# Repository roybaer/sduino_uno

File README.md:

# sduino UNO

The __sduino UNO__ is an attempt at creating a mechanically and electrically Arduino-UNO-compatible development board based on the __STM8S105K6__ microcontroller.
Both, mechanical and electrical design are to a notable degree based on the [Arduino UNO board](https://store.arduino.cc/arduino-uno-rev3).

Components and silkscreen can be viewed in more detail in a [picture of the component side](img/front.jpg) and a [picture of the back side](img/back.jpg) of the assembled board.

## Pin mapping

Number | UNO pin name | ATMEGA328 pin name | STM8S105K6 pin name
-------|--------------|--------------------|----------------------------------------
0      | IO0/RX       | PD0/RXD            | PD6/UART2_RX
1      | IO1/TX       | PD1/TXD            | PD5/UART2_TX
2      | IO2          | PD2/INT0           | PD7/TLI [TIM1_CH4]
3      | IO3          | PD3/INT1/OC2B      | PD2 (HS)/TIM3_CH1 [TIM2_CH3]
4      | IO4          | PD4/T0/XCK         | PD0 (HS)/TIM3_CH2 [TIM1_BKIN]/[CLK_COO]
5      | IO5          | PD5/T1/OC0B        | PD4 (HS)/TIM2_CH1 [BEEP]
6      | IO6          | PD6/AIN0/OC0A      | PD3 (HS)/TIM2_CH2/ADC_ETR
7      | IO7          | PD7/AIN1           | PD1 (HS)/SWIM
8      | IO8          | PB0/ICP1/CLKO      | PC1 (HS)/TIM1_CH1/UART2_CK
9      | IO9          | PB1/OC1A           | PC3 (HS)/TIM1_CH3
10     | IO10/~~SS~~  | PB2/NSS/OC1B       | PC4 (HS)/TIM1_CH4
11     | IO11/MOSI    | PB3/MOSI/OC2A      | PC6 (HS)/SPI_MOSI
12     | IO12/MISO    | PB4/MISO           | PC7 (HS)/SPI_MISO
13     | IO13/SCK     | PB5/SCK            | PC5 (HS)/SPI_SCK
14     | AD0          | PC0/ADC0           | PB0/AIN0 [TIM1_CH1N]
15     | AD1          | PC1/ADC1           | PB1/AIN1 [TIM1_CH2N]
16     | AD2          | PC2/ADC2           | PB2/AIN2 [TIM1_CH3N]
17     | AD3          | PC3/ADC3           | PB3/AIN3 [TIM1_ETR]
18     | AD4/SDA      | PC4/ADC4           | PB5/AIN5 [I2C_SDA]
19     | AD5/SCL      | PC5/ADC5           | PB4/AIN4 [I2C_SCL]
20     | AD6          | --                 | --
21     | AD7          | --                 | --
_22_   | AREF         | AREF               | PF4/AIN12
_23_   | _IO23_       | --                 | PC2 (HS)/TIM1_CH2
_24_   | _IO24/SS_    | --                 | PE5/SPI_NSS
--     | RESET        | NRESET             | NRST
--     | --           | PB6/TOSC1/XTAL1    | PA1/OSCIN
--     | --           | PB7/TOSC2/XTAL2    | PA2/OSCOUT

For evaluation purposes, most of the sduino UNO's functionality can be imitated with an STM8-DISCOVERY board and a USB to Serial converter, as described in [this document](docs/discovery.md).

## Differences

The following paragraphs highlight the most important differences between Arduino UNO and sduino UNO.

### Mechanical

The gap between the upper socket strips has been reduced from 0.06 to 0.05 inches.
This should not significantly impact mechanical compatibility with Arduino UNO shields and increases the available radius around the center of the upper left M3 mounting hole from 2.286 to 2.54 millimeters, which should be just enough to fit in a standard M3 spacer (5mm wrench).

### Electrical

Most importantly, the sduino UNO can be switched between 5V and 3.3V operating voltage.
The RX and TX LEDs are connected to the RX and TX lines (IO pin 0 and 1, respectively) via 1k resistors, rather than to the USB interface chip.

### Functional

Like many Arduino UNO clones, the sduino UNO uses a CH340G USB to serial converter instead of an Atmega16U2 for communication with the host PC.
The USB interface Chip therefore cannot be repurposed as a coprocessor or keyboard/mouse simulator.

There is no analog comparator in the STM8S105K6 microcontroller and AREF is actually an additional analog input.
Its use as reference voltage for A/D conversion has to be imitated in software.
IO11 has no hardware PWM functionality for analog_write, IO8 and IO4 have.
IO2, AD0, AD1 and AD2 can be used as PWM outputs via alternate function mapping.

Likewise, IO10 does not serve as hardware-slave-select line for the SPI bus.
This, however, can mostly be overcome by software-emulation, because the STM8 allows for slave-select to be controlled in software, e.g. in an interrupt handler.
The actual slave-select line has been made available via an exra pin.

### Software

Unfortunately, there is no free C++ compiler available for the STM8 platform, yet.
The Arduino language along with the large pool of existing Arduino sketches can therefore not be used without modifications.

Fortunately, there is the C-based [sduino library](https://github.com/tenbaht/sduino) that in fact inspired the creation of the sduino UNO and that this board borrows its name from.
By using the sduino library, the changes required to run many exsting Arduino sketches on an STM8 platform can be kept within manageable bounds.

Possibilities to bring C++ support to the STM8 platform with a free compiler are being evaluated.

## Copying

Even though the sduino UNO CAD files have been created from scratch and the design is not identical, to avoid legal ambiguity, the CAD files for the sduino UNO board are released under the same creative commons license as those of the Arduino UNO board:

This work is licensed under the Creative Commons Attribution-ShareAlike 2.5 Generic License. To view a copy of this license, visit http://creativecommons.org/licenses/by-sa/2.5/ or send a letter to Creative Commons, PO Box 1866, Mountain View, CA 94042, USA.

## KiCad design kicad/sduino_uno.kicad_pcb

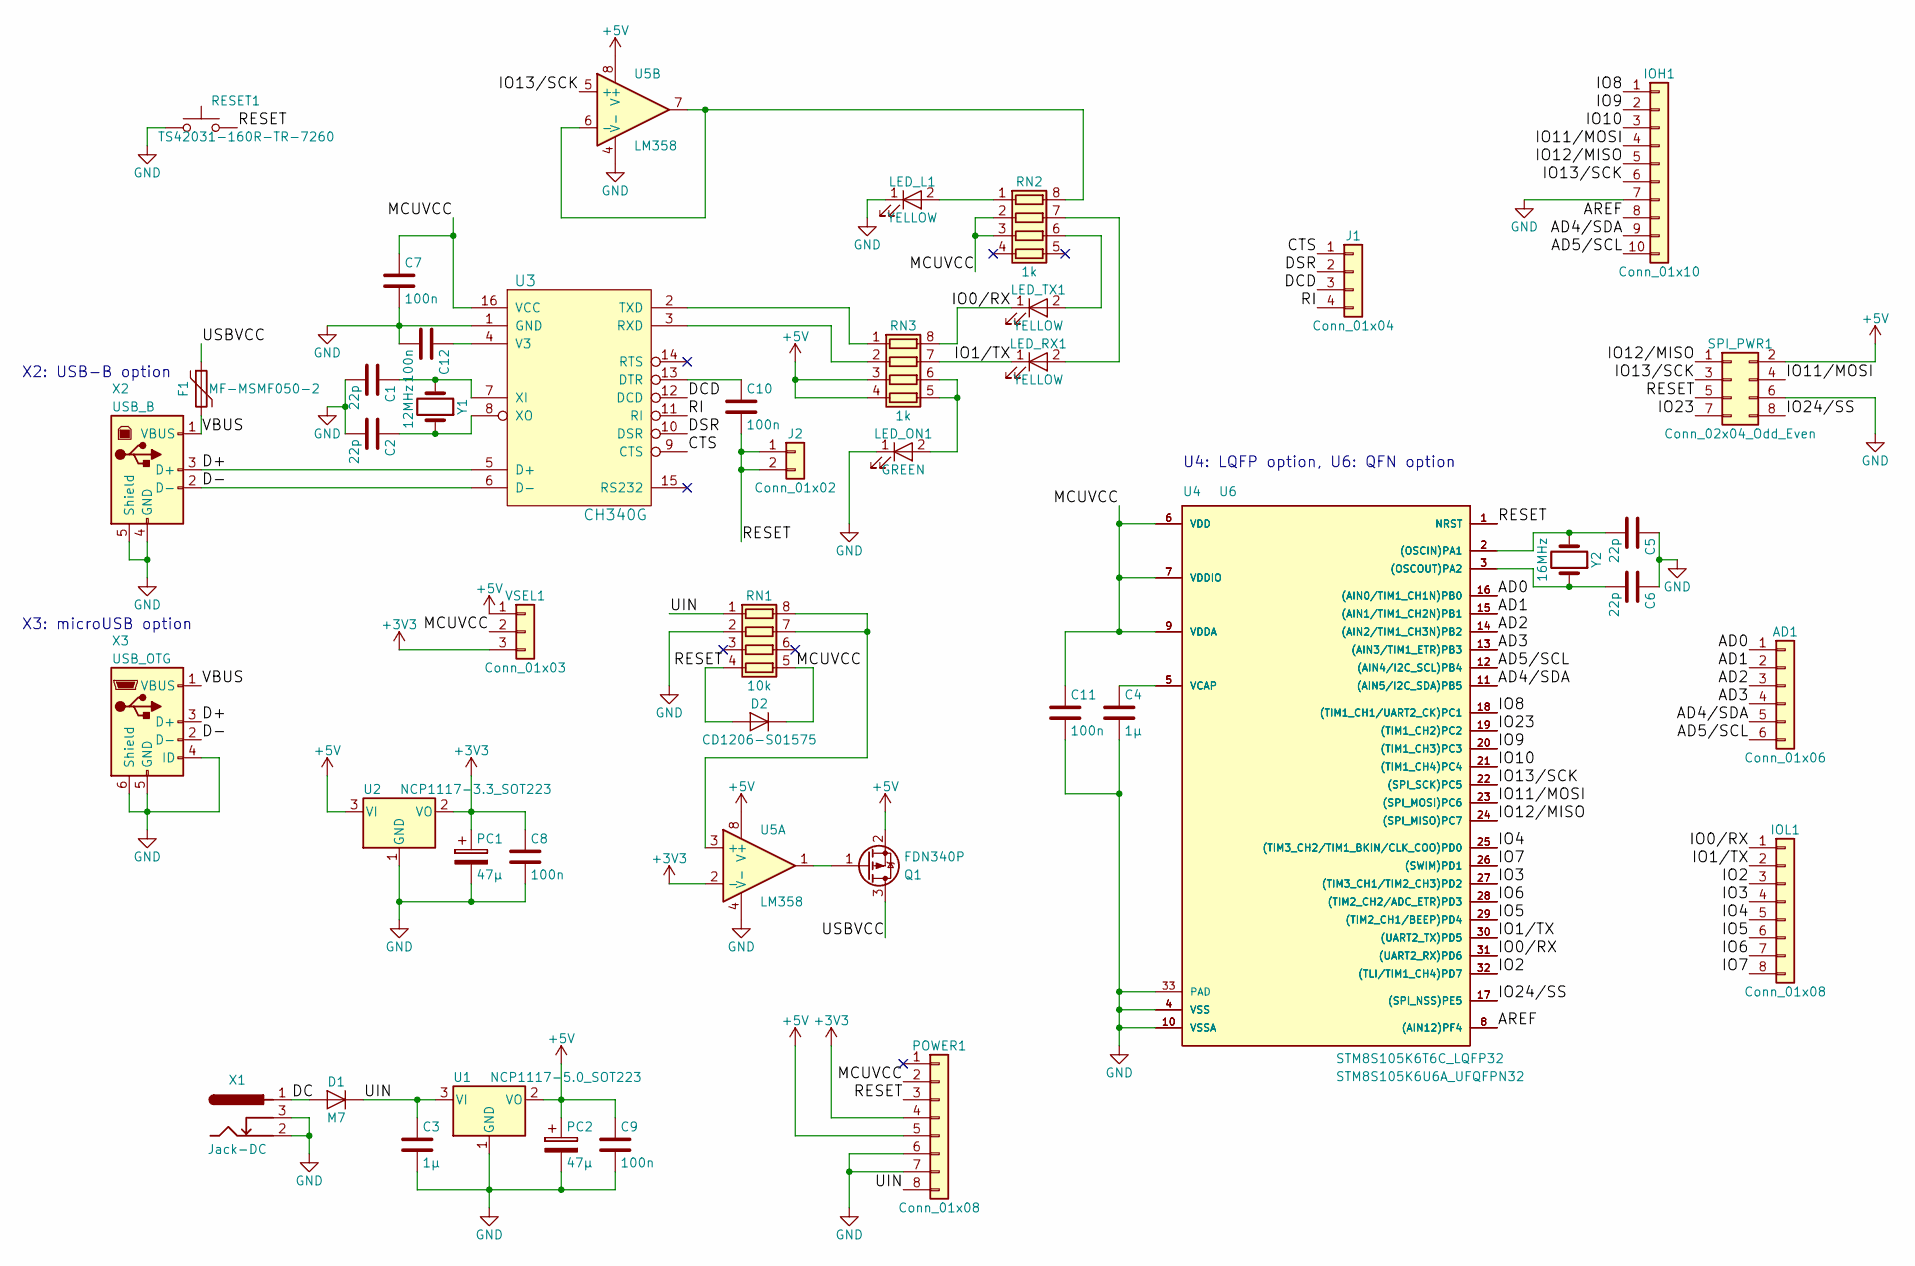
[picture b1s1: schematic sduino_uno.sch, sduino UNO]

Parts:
AD1: Conn_01x06; Socket_Strip_Straight_1x06_Pitch2.54mm
C1, C2, C5, C6: 22p; C_0603
C3, C4: 1µ; C_0805
C7, C8, C9, C10, C11, C12: 100n; C_0603
D1: M7; D_SMA
D2: CD1206-S01575; D_1206
F1: MF-MSMF050-2; R_1812
IOH1: Conn_01x10; Socket_Strip_Straight_1x10_Pitch2.54mm
IOL1: Conn_01x08; Socket_Strip_Straight_1x08_Pitch2.54mm
J1: Conn_01x04; Pin_Header_Straight_1x04_Pitch2.54mm
J2: Conn_01x02; Pin_Header_Straight_1x02_Pitch2.54mm
LED_L1: YELLOW; LED_0805
LED_ON1: GREEN; LED_0805
LED_RX1: YELLOW; LED_0805
LED_TX1: YELLOW; LED_0805
PC1, PC2: 47µ; CP_Elec_6.3x5.8
POWER1: Conn_01x08; Socket_Strip_Straight_1x08_Pitch2.54mm
Q1: FDN340P; SOT-23
RESET1: TS42031-160R-TR-7260; SW_SPST_B3S-1000
RN1: 10k; R_Array_Concave_4x0603
RN2, RN3: 1k; R_Array_Concave_4x0603
SPI_PWR1: Conn_02x04_Odd_Even; Pin_Header_Straight_2x04_Pitch2.54mm
U1: NCP1117-5.0_SOT223; SOT-223-3Lead_TabPin2
U2: NCP1117-3.3_SOT223; SOT-223-3Lead_TabPin2
U3: CH340G; SOIC-16_3.9x9.9mm_Pitch1.27mm
U4: STM8S105K6T6C_LQFP32; LQFP-32_7x7mm_Pitch0.8mm
U5: LM358; SOIC-8_3.9x4.9mm_Pitch1.27mm
U6: STM8S105K6U6A_UFQFPN32; QFN-32-1EP_5x5mm_Pitch0.5mm
VSEL1: Conn_01x03; Pin_Header_Straight_1x03_Pitch2.54mm
X1: Jack-DC; JACK_ALIM
X2: USB_B
X3: USB_OTG; USB_Micro-B_Molex_47346-0001
Y1: 12MHz; Crystal_HC49-4H_Vertical
Y2: 16MHz; Crystal_HC49-4H_Vertical

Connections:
+3V3: C8.1, PC1.1, POWER1.4, U2.2 (VO), U5.2 (-), VSEL1.3
+5V: C9.1, PC2.1, POWER1.5, Q1.2 (S), RN3.3 (R3.1), RN3.4 (R4.1), SPI_PWR1.2, U1.2 (VO), U2.3 (VI), U5.8 (V+), VSEL1.1
/AD0: AD1.1, U4.16 ((AIN0/TIM1_CH1N)PB0), U6.16 ((AIN0/TIM1_CH1N)PB0)
/AD1: AD1.2, U4.15 ((AIN1/TIM1_CH2N)PB1), U6.15 ((AIN1/TIM1_CH2N)PB1)
/AD2: AD1.3, U4.14 ((AIN2/TIM1_CH3N)PB2), U6.14 ((AIN2/TIM1_CH3N)PB2)
/AD3: AD1.4, U4.13 ((AIN3/TIM1_ETR)PB3), U6.13 ((AIN3/TIM1_ETR)PB3)
/AD4/SDA: AD1.5, IOH1.9, U4.11 ((AIN5/I2C_SDA)PB5), U6.11 ((AIN5/I2C_SDA)PB5)
/AD5/SCL: AD1.6, IOH1.10, U4.12 ((AIN4/I2C_SCL)PB4), U6.12 ((AIN4/I2C_SCL)PB4)
/AREF: IOH1.8, U4.8 ((AIN12)PF4), U6.8 ((AIN12)PF4)
/CTS: J1.1, U3.9 (CTS)
/D+: U3.5 (D+), X2.3 (D+), X3.3 (D+)
/D-: U3.6 (D-), X2.2 (D-), X3.2 (D-)
/DC: D1.2 (A), X1.1
/DCD: J1.3, U3.12 (DCD)
/DSR: J1.2, U3.10 (DSR)
/IO0/RX: IOL1.1, LED_TX1.1 (K), RN3.8 (R1.2), U4.31 ((UART2_RX)PD6), U6.31 ((UART2_RX)PD6)
/IO1/TX: IOL1.2, LED_RX1.1 (K), RN3.7 (R2.2), U4.30 ((UART2_TX)PD5), U6.30 ((UART2_TX)PD5)
/IO2: IOL1.3, U4.32 ((TLI/TIM1_CH4)PD7), U6.32 ((TLI/TIM1_CH4)PD7)
/IO3: IOL1.4, U4.27 ((TIM3_CH1/TIM2_CH3)PD2), U6.27 ((TIM3_CH1/TIM2_CH3)PD2)
/IO4: IOL1.5, U4.25 ((TIM3_CH2/TIM1_BKIN/CLK_COO)PD0), U6.25 ((TIM3_CH2/TIM1_BKIN/CLK_COO)PD0)
/IO5: IOL1.6, U4.29 ((TIM2_CH1/BEEP)PD4), U6.29 ((TIM2_CH1/BEEP)PD4)
/IO6: IOL1.7, U4.28 ((TIM2_CH2/ADC_ETR)PD3), U6.28 ((TIM2_CH2/ADC_ETR)PD3)
/IO7: IOL1.8, U4.26 ((SWIM)PD1), U6.26 ((SWIM)PD1)
/IO8: IOH1.1, U4.18 ((TIM1_CH1/UART2_CK)PC1), U6.18 ((TIM1_CH1/UART2_CK)PC1)
/IO9: IOH1.2, U4.20 ((TIM1_CH3)PC3), U6.20 ((TIM1_CH3)PC3)
/IO10: IOH1.3, U4.21 ((TIM1_CH4)PC4), U6.21 ((TIM1_CH4)PC4)
/IO11/MOSI: IOH1.4, SPI_PWR1.4, U4.23 ((SPI_MOSI)PC6), U6.23 ((SPI_MOSI)PC6)
/IO12/MISO: IOH1.5, SPI_PWR1.1, U4.24 ((SPI_MISO)PC7), U6.24 ((SPI_MISO)PC7)
/IO13/SCK: IOH1.6, SPI_PWR1.3, U4.22 ((SPI_SCK)PC5), U5.5 (+), U6.22 ((SPI_SCK)PC5)
/IO23: SPI_PWR1.7, U4.19 ((TIM1_CH2)PC2), U6.19 ((TIM1_CH2)PC2)
/IO24/SS: SPI_PWR1.8, U4.17 ((SPI_NSS)PE5), U6.17 ((SPI_NSS)PE5)
/MCUVCC: C7.1, C11.1, D2.1 (K), POWER1.2, RN1.5 (R4.2), RN2.2 (R2.1), RN2.3 (R3.1), U3.16 (VCC), U4.6 (VDD), U4.7 (VDDIO), U4.9 (VDDA), U6.6 (VDD), U6.7 (VDDIO), U6.9 (VDDA), VSEL1.2
/RESET: C10.2, D2.2 (A), J2.1, J2.2, POWER1.3, RESET1.2, RN1.4 (R4.1), SPI_PWR1.5, U4.1 (NRST), U6.1 (NRST)
/RI: J1.4, U3.11 (RI)
/UIN: C3.1, D1.1 (K), POWER1.8, RN1.1 (R1.1), U1.3 (VI)
/USBVCC: F1.1, Q1.3 (D)
/VBUS: F1.2, X2.1 (VBUS), X3.1 (VBUS)
GND: C1.2, C2.2, C3.2, C4.2, C5.1, C6.1, C7.2, C8.2, C9.2, C11.2, C12.2, IOH1.7, LED_L1.1 (K), LED_ON1.1 (K), PC1.2, PC2.2, POWER1.6, POWER1.7, RESET1.1, RN1.2 (R2.1), SPI_PWR1.6, U1.1 (GND), U2.1 (GND), U3.1 (GND), U4.4 (VSS), U4.10 (VSSA), U5.4 (V-), U6.4 (VSS), U6.10 (VSSA), U6.33 (PAD), X1.2, X1.3, X2.4 (GND), X2.5 (Shield), X3.4 (ID), X3.5 (GND), X3.6 (Shield)
unnamed: C1.1, U3.7 (XI), Y1.2
unnamed: C2.1, U3.8 (XO), Y1.1
unnamed: C4.1, U4.5 (VCAP), U6.5 (VCAP)
unnamed: C5.2, U4.2 ((OSCIN)PA1), U6.2 ((OSCIN)PA1), Y2.2
unnamed: C6.2, U4.3 ((OSCOUT)PA2), U6.3 ((OSCOUT)PA2), Y2.1
unnamed: C10.1, U3.13 (DTR)
unnamed: C12.1, U3.4 (V3)
unnamed: LED_L1.2 (A), RN2.1 (R1.1)
unnamed: LED_ON1.2 (A), RN3.5 (R4.2), RN3.6 (R3.2)
unnamed: LED_RX1.2 (A), RN2.7 (R2.2)
unnamed: LED_TX1.2 (A), RN2.6 (R3.2)
unnamed: Q1.1 (G), U5.1
unnamed: RN1.7 (R2.2), RN1.8 (R1.2), U5.3 (+)
unnamed: RN2.8 (R1.2), U5.6 (-), U5.7
unnamed: RN3.1 (R1.1), U3.2 (TXD)
unnamed: RN3.2 (R2.1), U3.3 (RXD)

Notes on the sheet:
U4: LQFP option, U6: QFN option
X2: USB-B option
X3: microUSB option

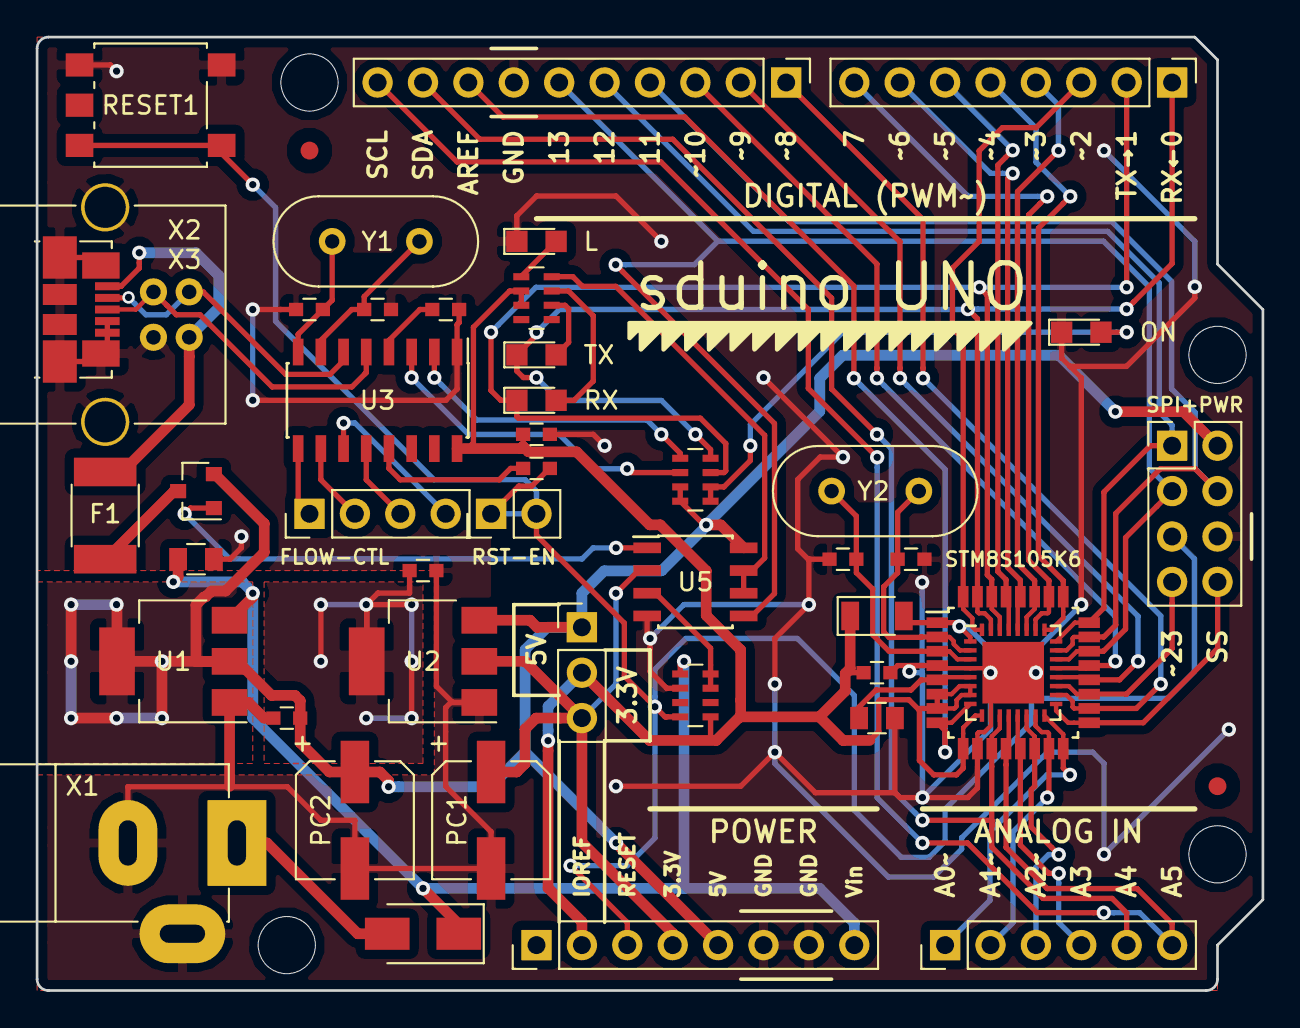
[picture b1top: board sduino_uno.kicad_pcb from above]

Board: 2 copper layers, 68.6 x 53.3 mm, 45 parts (0 on the bottom side), 54 nets.

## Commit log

2017-10-06 board revision 2017-10-01 and documentation
2017-10-07 improve documentation
2017-10-08 revision 2017-10-08 - fix major error in TX/RX wiring (LEDs were connected in series) - improve ground fill surrounding crystals - rename IO14 to IO23 - add some pin numbers on the back side - update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
2017-10-10 board revision 2017-10-10 (minor PCB changes) - optimized ground fills - reduced thermal relief around the regulators' thermal pads
2017-10-12 update and extend documentation
2017-10-12 fix link
2017-10-30 remove stm8.bck and add *.bck to .gitignore
2017-11-11 photo of board revision 2017-10-10
2017-11-15 board revision 2017-11-15 (minor corrections and clarifications)
    - use more precise names for some components
    - adjust footprint of DC jack to better fit the DC jack
    - adjust thermal relief around pads of 0603 components
2017-11-18 add more pictures

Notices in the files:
kicad/sduino_uno.kicad_pcb:
see http://creativecommons.org/licenses/by-sa/2.5
Released under Creative Commons Attribution-ShareAlike 2.5 Generic License,
